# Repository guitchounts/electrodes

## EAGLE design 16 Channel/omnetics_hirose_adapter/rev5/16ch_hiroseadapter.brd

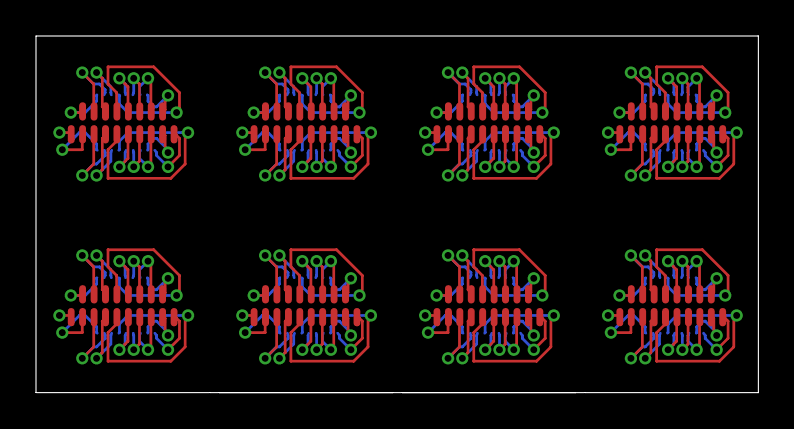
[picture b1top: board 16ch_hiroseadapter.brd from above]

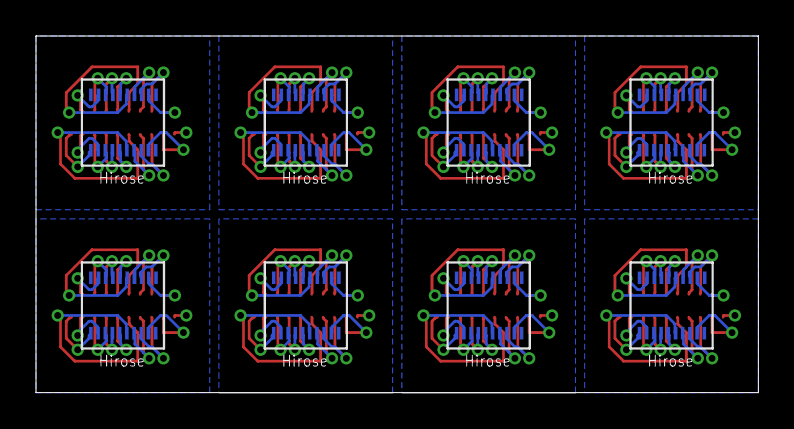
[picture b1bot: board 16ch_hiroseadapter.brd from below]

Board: 2 copper layers, 40.1 x 19.8 mm, 16 parts (8 on the bottom side), 144 nets.

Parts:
U$1, U$3, U$5, U$7, U$9, U$11, U$13, U$15: HIROSE_DF40_70PIN; HIROSE_DF40C-70DS
U$2, U$4, U$6, U$8, U$10, U$12, U$14, U$16: OMNETICS_FE18

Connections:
unnamed: U$1.P$10, U$2.P$18
unnamed: U$1.P$9, U$2.P$8
unnamed: U$1.P$8, U$2.P$7
unnamed: U$1.P$7, U$2.P$6
unnamed: U$1.P$6, U$2.P$5
unnamed: U$1.P$5, U$2.P$4
unnamed: U$1.P$4, U$2.P$3
unnamed: U$1.P$3, U$2.P$2
unnamed: U$1.P$2, U$2.P$1
unnamed: U$1.P$1, U$2.P$17
unnamed: U$1.P$44, U$2.P$9
unnamed: U$1.P$43, U$2.P$10
unnamed: U$1.P$42, U$2.P$11
unnamed: U$1.P$41, U$2.P$12
unnamed: U$1.P$40, U$2.P$13
unnamed: U$1.P$39, U$2.P$14
unnamed: U$1.P$38, U$2.P$15
unnamed: U$1.P$37, U$2.P$16
unnamed: U$3.P$10, U$4.P$18
unnamed: U$3.P$9, U$4.P$8
unnamed: U$3.P$8, U$4.P$7
unnamed: U$3.P$7, U$4.P$6
unnamed: U$3.P$6, U$4.P$5
unnamed: U$3.P$5, U$4.P$4
unnamed: U$3.P$4, U$4.P$3
unnamed: U$3.P$3, U$4.P$2
unnamed: U$3.P$2, U$4.P$1
unnamed: U$3.P$1, U$4.P$17
unnamed: U$3.P$44, U$4.P$9
unnamed: U$3.P$43, U$4.P$10
unnamed: U$3.P$42, U$4.P$11
unnamed: U$3.P$41, U$4.P$12
unnamed: U$3.P$40, U$4.P$13
unnamed: U$3.P$39, U$4.P$14
unnamed: U$3.P$38, U$4.P$15
unnamed: U$3.P$37, U$4.P$16
unnamed: U$5.P$10, U$6.P$18
unnamed: U$5.P$9, U$6.P$8
unnamed: U$5.P$8, U$6.P$7
unnamed: U$5.P$7, U$6.P$6
unnamed: U$5.P$6, U$6.P$5
unnamed: U$5.P$5, U$6.P$4
unnamed: U$5.P$4, U$6.P$3
unnamed: U$5.P$3, U$6.P$2
unnamed: U$5.P$2, U$6.P$1
unnamed: U$5.P$1, U$6.P$17
unnamed: U$5.P$44, U$6.P$9
unnamed: U$5.P$43, U$6.P$10
unnamed: U$5.P$42, U$6.P$11
unnamed: U$5.P$41, U$6.P$12
unnamed: U$5.P$40, U$6.P$13
unnamed: U$5.P$39, U$6.P$14
unnamed: U$5.P$38, U$6.P$15
unnamed: U$5.P$37, U$6.P$16
unnamed: U$7.P$10, U$8.P$18
unnamed: U$7.P$9, U$8.P$8
unnamed: U$7.P$8, U$8.P$7
unnamed: U$7.P$7, U$8.P$6
unnamed: U$7.P$6, U$8.P$5
unnamed: U$7.P$5, U$8.P$4
unnamed: U$7.P$4, U$8.P$3
unnamed: U$7.P$3, U$8.P$2
unnamed: U$7.P$2, U$8.P$1
unnamed: U$7.P$1, U$8.P$17
unnamed: U$7.P$44, U$8.P$9
unnamed: U$7.P$43, U$8.P$10
unnamed: U$7.P$42, U$8.P$11
unnamed: U$7.P$41, U$8.P$12
unnamed: U$7.P$40, U$8.P$13
unnamed: U$7.P$39, U$8.P$14
unnamed: U$7.P$38, U$8.P$15
unnamed: U$7.P$37, U$8.P$16
unnamed: U$9.P$10, U$10.P$18
unnamed: U$9.P$9, U$10.P$8
unnamed: U$9.P$8, U$10.P$7
unnamed: U$9.P$7, U$10.P$6
unnamed: U$9.P$6, U$10.P$5
unnamed: U$9.P$5, U$10.P$4
unnamed: U$9.P$4, U$10.P$3
unnamed: U$9.P$3, U$10.P$2
unnamed: U$9.P$2, U$10.P$1
unnamed: U$9.P$1, U$10.P$17
unnamed: U$9.P$44, U$10.P$9
unnamed: U$9.P$43, U$10.P$10
unnamed: U$9.P$42, U$10.P$11
unnamed: U$9.P$41, U$10.P$12
unnamed: U$9.P$40, U$10.P$13
unnamed: U$9.P$39, U$10.P$14
unnamed: U$9.P$38, U$10.P$15
unnamed: U$9.P$37, U$10.P$16
unnamed: U$11.P$10, U$12.P$18
unnamed: U$11.P$9, U$12.P$8
unnamed: U$11.P$8, U$12.P$7
unnamed: U$11.P$7, U$12.P$6
unnamed: U$11.P$6, U$12.P$5
unnamed: U$11.P$5, U$12.P$4
unnamed: U$11.P$4, U$12.P$3
unnamed: U$11.P$3, U$12.P$2
unnamed: U$11.P$2, U$12.P$1
unnamed: U$11.P$1, U$12.P$17
unnamed: U$11.P$44, U$12.P$9
unnamed: U$11.P$43, U$12.P$10
unnamed: U$11.P$42, U$12.P$11
unnamed: U$11.P$41, U$12.P$12
unnamed: U$11.P$40, U$12.P$13
unnamed: U$11.P$39, U$12.P$14
unnamed: U$11.P$38, U$12.P$15
unnamed: U$11.P$37, U$12.P$16
unnamed: U$13.P$10, U$14.P$18
unnamed: U$13.P$9, U$14.P$8
unnamed: U$13.P$8, U$14.P$7
unnamed: U$13.P$7, U$14.P$6
unnamed: U$13.P$6, U$14.P$5
unnamed: U$13.P$5, U$14.P$4
unnamed: U$13.P$4, U$14.P$3
unnamed: U$13.P$3, U$14.P$2
unnamed: U$13.P$2, U$14.P$1
unnamed: U$13.P$1, U$14.P$17
unnamed: U$13.P$44, U$14.P$9
unnamed: U$13.P$43, U$14.P$10
unnamed: U$13.P$42, U$14.P$11
unnamed: U$13.P$41, U$14.P$12
unnamed: U$13.P$40, U$14.P$13
unnamed: U$13.P$39, U$14.P$14
unnamed: U$13.P$38, U$14.P$15
unnamed: U$13.P$37, U$14.P$16
unnamed: U$15.P$10, U$16.P$18
unnamed: U$15.P$9, U$16.P$8
unnamed: U$15.P$8, U$16.P$7
unnamed: U$15.P$7, U$16.P$6
unnamed: U$15.P$6, U$16.P$5
unnamed: U$15.P$5, U$16.P$4
unnamed: U$15.P$4, U$16.P$3
unnamed: U$15.P$3, U$16.P$2
unnamed: U$15.P$2, U$16.P$1
unnamed: U$15.P$1, U$16.P$17
unnamed: U$15.P$44, U$16.P$9
unnamed: U$15.P$43, U$16.P$10
unnamed: U$15.P$42, U$16.P$11
unnamed: U$15.P$41, U$16.P$12
unnamed: U$15.P$40, U$16.P$13
unnamed: U$15.P$39, U$16.P$14
unnamed: U$15.P$38, U$16.P$15
unnamed: U$15.P$37, U$16.P$16

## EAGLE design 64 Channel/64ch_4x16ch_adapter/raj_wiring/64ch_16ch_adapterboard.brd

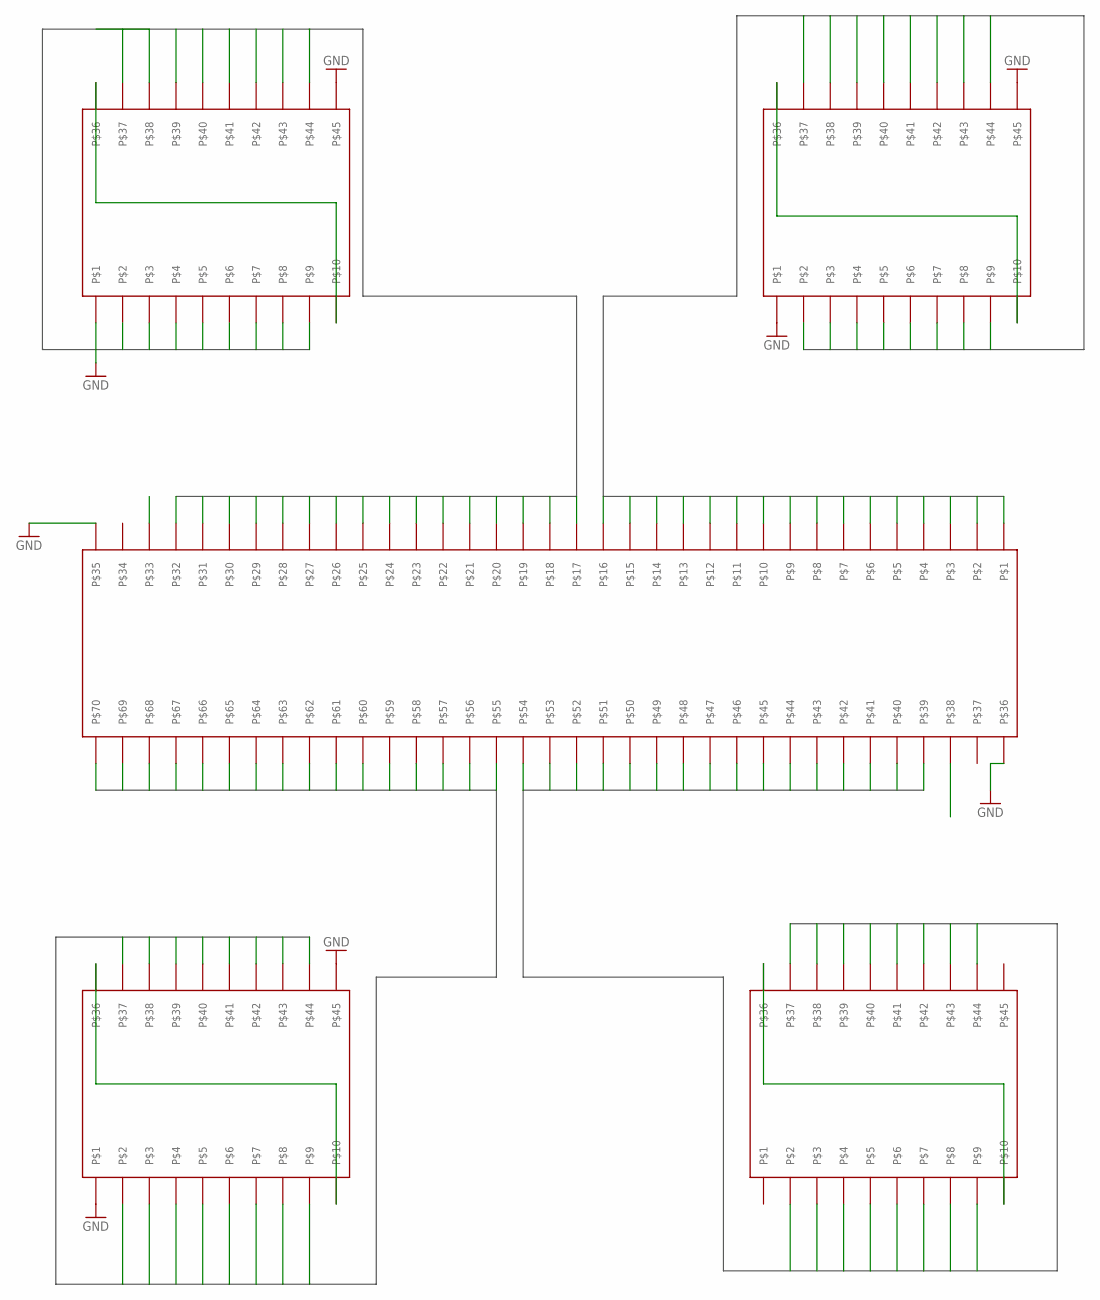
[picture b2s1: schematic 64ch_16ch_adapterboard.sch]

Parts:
U$1: HIROSE_DF40_70PIN; HIROSE_DF40C-70DS
U$2, U$3, U$4, U$5: HIROSE_DF40_20PIN; HIROSE_DF40C-70DS

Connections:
A0: U$1.P$18, U$3.P$44
A1: U$1.P$17, U$3.P$9
A2: U$1.P$32, U$3.P$8
A3: U$1.P$31, U$3.P$7
A4: U$1.P$30, U$3.P$6
A5: U$1.P$29, U$3.P$5
A6: U$1.P$28, U$3.P$4
A7: U$1.P$27, U$3.P$3
A8: U$1.P$26, U$3.P$2
A9: U$1.P$25, U$3.P$37
A10: U$1.P$22, U$3.P$38
A11: U$1.P$21, U$3.P$39
A12: U$1.P$23, U$3.P$40
A13: U$1.P$20, U$3.P$41
A14: U$1.P$24, U$3.P$42
A15: U$1.P$19, U$3.P$43
B0: U$1.P$3, U$2.P$37
B1: U$1.P$4, U$2.P$2
B2: U$1.P$5, U$2.P$3
B3: U$1.P$6, U$2.P$4
B4: U$1.P$7, U$2.P$5
B5: U$1.P$8, U$2.P$6
B6: U$1.P$9, U$2.P$7
B7: U$1.P$10, U$2.P$8
B8: U$1.P$11, U$2.P$9
B9: U$1.P$12, U$2.P$44
B10: U$1.P$15, U$2.P$43
B11: U$1.P$16, U$2.P$42
B12: U$1.P$14, U$2.P$41
B13: U$1.P$1, U$2.P$40
B14: U$1.P$13, U$2.P$39
B15: U$1.P$2, U$2.P$38
C0: U$1.P$69, U$5.P$9
C1: U$1.P$68, U$5.P$44
C2: U$1.P$67, U$5.P$43
C3: U$1.P$66, U$5.P$42
C4: U$1.P$65, U$5.P$41
C5: U$1.P$64, U$5.P$40
C6: U$1.P$63, U$5.P$39
C7: U$1.P$62, U$5.P$38
C8: U$1.P$61, U$5.P$37
C9: U$1.P$60, U$5.P$2
C10: U$1.P$57, U$5.P$3
C11: U$1.P$56, U$5.P$4
C12: U$1.P$58, U$5.P$5
C13: U$1.P$55, U$5.P$6
C14: U$1.P$59, U$5.P$7
C15: U$1.P$70, U$5.P$8
D0: U$1.P$54, U$4.P$2
D1: U$1.P$39, U$4.P$37
D2: U$1.P$40, U$4.P$38
D3: U$1.P$41, U$4.P$39
D4: U$1.P$42, U$4.P$40
D5: U$1.P$43, U$4.P$41
D6: U$1.P$44, U$4.P$42
D7: U$1.P$45, U$4.P$43
D8: U$1.P$46, U$4.P$44
D9: U$1.P$47, U$4.P$9
D10: U$1.P$50, U$4.P$8
D11: U$1.P$51, U$4.P$7
D12: U$1.P$49, U$4.P$6
D13: U$1.P$52, U$4.P$5
D14: U$1.P$48, U$4.P$4
D15: U$1.P$53, U$4.P$3
GND: U$1.P$35, U$1.P$36, U$2.P$1, U$2.P$45, U$3.P$1, U$3.P$45, U$5.P$1, U$5.P$45
REF: U$1.P$33, U$1.P$38, U$2.P$10, U$2.P$36, U$3.P$10, U$3.P$36, U$4.P$10, U$4.P$36, U$5.P$10, U$5.P$36

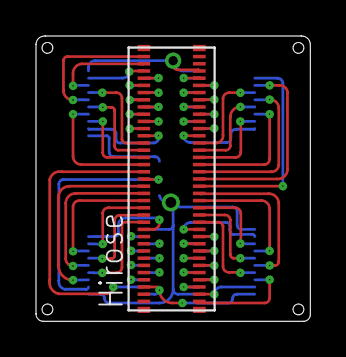
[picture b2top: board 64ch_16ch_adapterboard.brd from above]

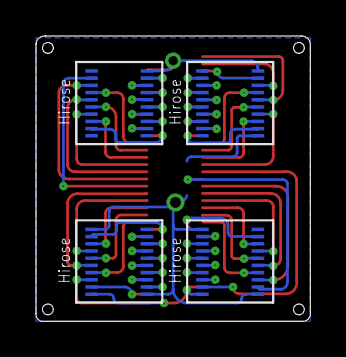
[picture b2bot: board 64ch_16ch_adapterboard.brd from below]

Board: 2 copper layers, 15.2 x 15.8 mm, 5 parts (4 on the bottom side), 66 nets.

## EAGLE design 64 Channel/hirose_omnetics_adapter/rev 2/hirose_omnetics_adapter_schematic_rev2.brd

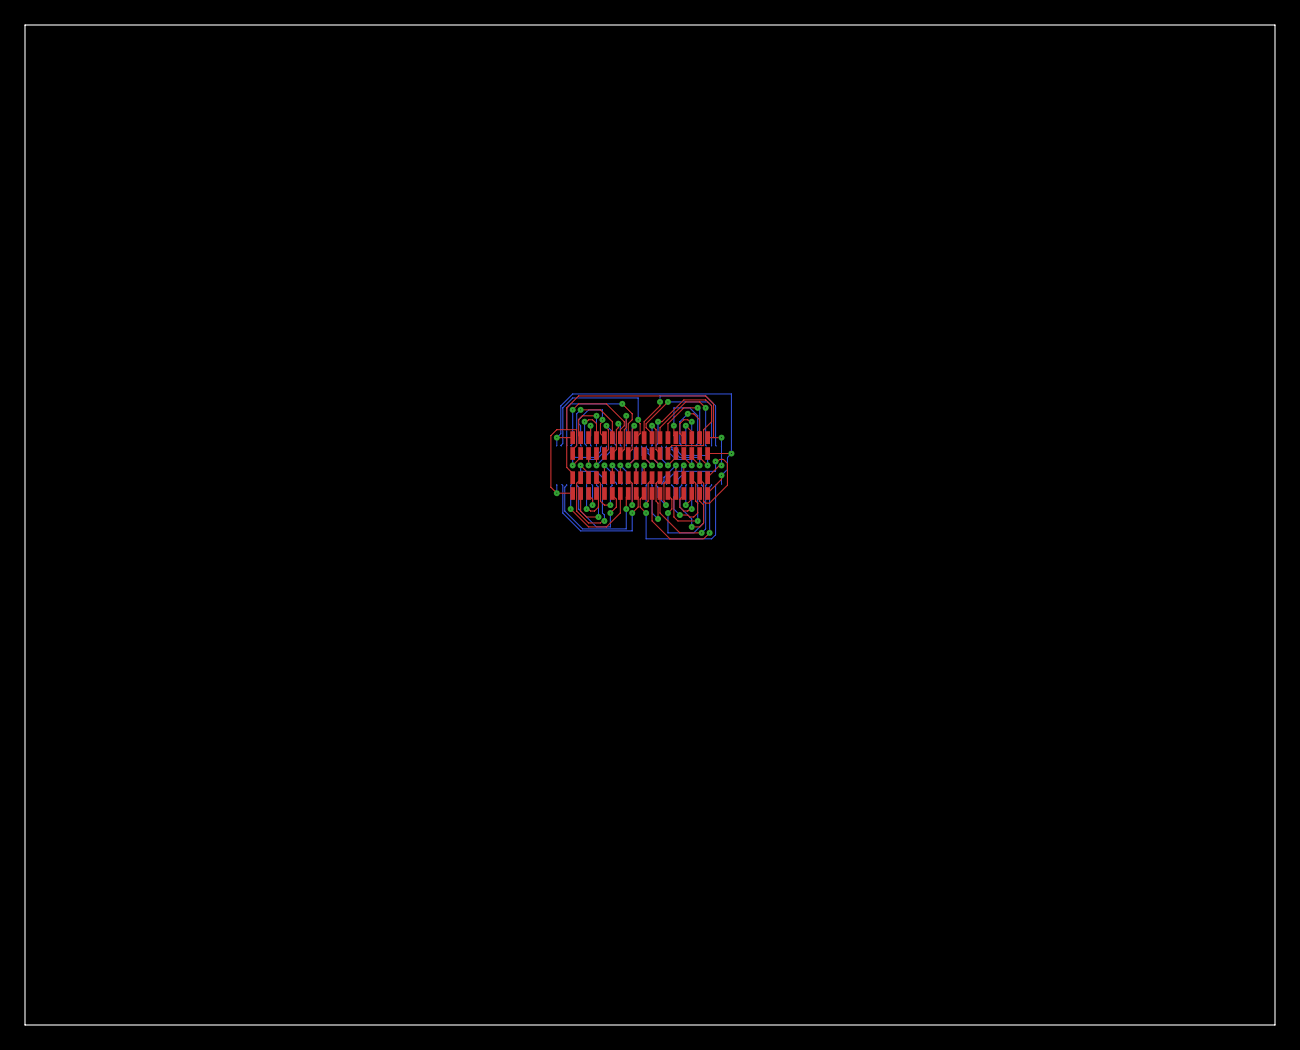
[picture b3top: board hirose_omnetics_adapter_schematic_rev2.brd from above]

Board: 2 copper layers, 100.0 x 80.0 mm, 3 parts (1 on the bottom side), 66 nets.

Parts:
U$1: HIROSE_DF40_70PIN; HIROSE_DF40C-70DS
U$2, U$3: OMNETICS_A79026; OMNETICS_A79026-001

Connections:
A0: U$1.P$69, U$2.P$10
A1: U$1.P$68, U$2.P$11
A2: U$1.P$67, U$2.P$12
A3: U$1.P$66, U$2.P$13
A4: U$1.P$65, U$2.P$14
A5: U$1.P$64, U$2.P$15
A6: U$1.P$63, U$2.P$16
A7: U$1.P$62, U$2.P$17
B0: U$1.P$38, U$2.P$9
B1: U$1.P$39, U$2.P$8
B2: U$1.P$40, U$2.P$7
B3: U$1.P$41, U$2.P$6
B4: U$1.P$42, U$2.P$5
B5: U$1.P$43, U$2.P$4
B6: U$1.P$44, U$2.P$3
B7: U$1.P$45, U$2.P$2
C0: U$1.P$34, U$3.P$28
C1: U$1.P$33, U$3.P$29
C2: U$1.P$32, U$3.P$30
C3: U$1.P$31, U$3.P$31
C4: U$1.P$30, U$3.P$32
C5: U$1.P$29, U$3.P$33
C6: U$1.P$28, U$3.P$34
C7: U$1.P$27, U$3.P$35
D0: U$1.P$3, U$3.P$27
D1: U$1.P$4, U$3.P$26
D2: U$1.P$5, U$3.P$25
D3: U$1.P$6, U$3.P$24
D4: U$1.P$7, U$3.P$23
D5: U$1.P$8, U$3.P$22
D6: U$1.P$9, U$3.P$21
D7: U$1.P$10, U$3.P$20
GND: U$1.P$35, U$1.P$37, U$2.P$1, U$2.P$36, U$3.P$1, U$3.P$36
unnamed: U$1.P$61, U$2.P$35
unnamed: U$1.P$2, U$1.P$70, U$2.P$18, U$2.P$19, U$3.P$18, U$3.P$19
unnamed: U$1.P$60, U$2.P$34
unnamed: U$1.P$59, U$2.P$33
unnamed: U$1.P$58, U$2.P$32
unnamed: U$1.P$57, U$2.P$31
unnamed: U$1.P$56, U$2.P$30
unnamed: U$1.P$55, U$2.P$29
unnamed: U$1.P$54, U$2.P$28
unnamed: U$1.P$53, U$2.P$27
unnamed: U$1.P$52, U$2.P$26
unnamed: U$1.P$51, U$2.P$25
unnamed: U$1.P$50, U$2.P$24
unnamed: U$1.P$49, U$2.P$23
unnamed: U$1.P$48, U$2.P$22
unnamed: U$1.P$47, U$2.P$21
unnamed: U$1.P$46, U$2.P$20
unnamed: U$1.P$26, U$3.P$17
unnamed: U$1.P$25, U$3.P$16
unnamed: U$1.P$24, U$3.P$15
unnamed: U$1.P$23, U$3.P$14
unnamed: U$1.P$22, U$3.P$13
unnamed: U$1.P$21, U$3.P$12
unnamed: U$1.P$20, U$3.P$11
unnamed: U$1.P$19, U$3.P$10
unnamed: U$1.P$18, U$3.P$9
unnamed: U$1.P$17, U$3.P$8
unnamed: U$1.P$16, U$3.P$7
unnamed: U$1.P$15, U$3.P$6
unnamed: U$1.P$14, U$3.P$5
unnamed: U$1.P$13, U$3.P$4
unnamed: U$1.P$12, U$3.P$3
unnamed: U$1.P$11, U$3.P$2

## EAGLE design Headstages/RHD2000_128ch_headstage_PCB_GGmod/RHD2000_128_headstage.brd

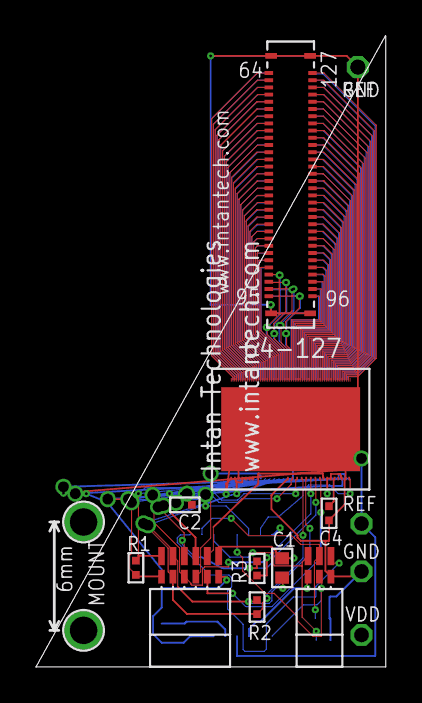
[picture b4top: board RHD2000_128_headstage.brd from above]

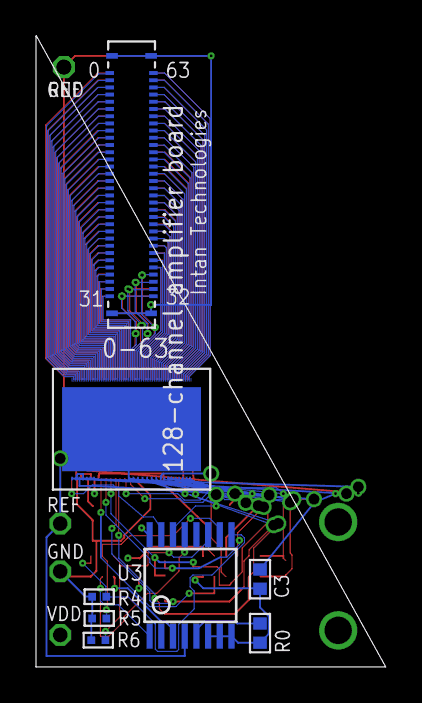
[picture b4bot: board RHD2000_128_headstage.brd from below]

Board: 4 copper layers, 19.4 x 35.1 mm, 25 parts (9 on the bottom side), 151 nets.

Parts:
C1, C3: 100n; 0402
C2, C4: 10n; 0201
GND, GND.: TESTPOINT_SMALL
H1, H2: MOUNTING_HOLE_60MIL
R0: 0; 0402
R1, R2, R3: 100; 0201
R4, R5, R6: 100k; 0201
REF, REF.: TESTPOINT_SMALL
S1, S2: MOLEX_SLIMSTACK_64
S3: RHD2000-CABLE-AMP-SIDE; OMNETICS_PZN-12-AA
S4: OMNETICS_PZN-06_SMD; OMNETICS_PZN-06-AA
U1, U2: RHD2164_COB
U3: 74HC4053_TSSOP-16; TSSOP-16
VDD: TESTPOINT_SMALL

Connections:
CS+: R1.2, S3.T1, U1.B10, U2.B10
CS-: R1.1, S3.B1, U1.B9, U2.B9
ELEC_TEST1: U1.B23, U3.14
ELEC_TEST2: U2.B23, U3.15
GND: C1.2, C2.2, C3.2, C4.2, GND.1, GND..1, R0.1, R4.1, R5.1, R6.1, S1.MECH1, S1.MECH2, S1.MECH3, S1.MECH4, S2.MECH1, S2.MECH2, S2.MECH3, S2.MECH4, S3.B6, S4.B3, U1.B3, U1.B8, U1.B22, U1.CENTER, U2.B3, U2.B8, U2.B22, U2.CENTER, U3.6, U3.7, U3.8
MISO1+: S3.T4, U1.B16
MISO1-: S3.B4, U1.B15
MISO2+: S3.T5, U2.B16
MISO2-: S3.B5, U2.B15
MOSI+: R3.2, S3.T3, U1.B14, U2.B14
MOSI-: R3.1, S3.B3, U1.B13, U2.B13
unnamed: C4.1, U2.B19
unnamed: S1.1, U1.0
unnamed: S1.2, U1.1
unnamed: S1.3, U1.2
unnamed: S1.4, U1.3
unnamed: S1.5, U1.4
unnamed: S1.6, U1.5
unnamed: S1.7, U1.6
unnamed: S1.8, U1.7
unnamed: S1.9, U1.8
unnamed: S2.1, U2.0
unnamed: S1.10, U1.9
unnamed: S1.11, U1.10
unnamed: S1.12, U1.11
unnamed: S1.13, U1.12
unnamed: S1.14, U1.13
unnamed: S1.15, U1.14
unnamed: S1.16, U1.15
unnamed: S1.17, U1.16
unnamed: S1.18, U1.17
unnamed: S1.19, U1.18
unnamed: S1.20, U1.19
unnamed: S1.21, U1.20
unnamed: S1.22, U1.21
unnamed: S1.23, U1.22
unnamed: S1.24, U1.23
unnamed: S1.25, U1.24
unnamed: S1.26, U1.25
unnamed: S1.27, U1.26
unnamed: S1.28, U1.27
unnamed: S1.38, U1.37
unnamed: S1.39, U1.38
unnamed: S1.64, U1.63
unnamed: S1.63, U1.62
unnamed: S2.2, U2.1
unnamed: S2.3, U2.2
unnamed: S2.4, U2.3
unnamed: S2.5, U2.4
unnamed: S2.6, U2.5
unnamed: S2.7, U2.6
unnamed: S1.62, U1.61
unnamed: C2.1, U1.B19
unnamed: S1.61, U1.60
unnamed: S1.60, U1.59
unnamed: S1.59, U1.58
unnamed: S1.58, U1.57
unnamed: S1.57, U1.56
unnamed: S1.56, U1.55
unnamed: S1.55, U1.54
unnamed: S1.54, U1.53
unnamed: S1.53, U1.52
unnamed: S1.52, U1.51
unnamed: S1.51, U1.50
unnamed: S1.50, U1.49
unnamed: S1.49, U1.48
unnamed: S1.48, U1.47
unnamed: S1.47, U1.46
unnamed: S1.46, U1.45
unnamed: S1.45, U1.44
unnamed: S1.44, U1.43
unnamed: S1.43, U1.42
unnamed: S1.42, U1.41
unnamed: S1.41, U1.40
unnamed: S1.40, U1.39
unnamed: S1.32, U1.31
unnamed: S1.31, U1.30
unnamed: S1.30, U1.29
unnamed: S1.29, U1.28
unnamed: S1.33, U1.32
unnamed: S1.34, U1.33
unnamed: S1.35, U1.34
unnamed: S1.36, U1.35
unnamed: S1.37, U1.36
unnamed: S2.8, U2.7
unnamed: S2.9, U2.8
unnamed: S2.10, U2.9
unnamed: S2.11, U2.10
unnamed: S2.12, U2.11
unnamed: S2.13, U2.12
unnamed: S2.14, U2.13
unnamed: S2.15, U2.14
unnamed: S2.16, U2.15
unnamed: S2.17, U2.16
unnamed: S2.18, U2.17
unnamed: S2.19, U2.18
unnamed: S2.20, U2.19
unnamed: S2.21, U2.20
unnamed: S2.22, U2.21
unnamed: S2.23, U2.22
unnamed: S2.24, U2.23
unnamed: S2.25, U2.24
unnamed: S2.26, U2.25
unnamed: S2.27, U2.26
unnamed: S2.28, U2.27
unnamed: S2.38, U2.37
unnamed: S2.39, U2.38
unnamed: S2.64, U2.63
unnamed: S2.63, U2.62
unnamed: S2.62, U2.61
unnamed: S2.61, U2.60
unnamed: S2.60, U2.59
unnamed: S2.59, U2.58
unnamed: S2.58, U2.57
unnamed: S2.57, U2.56
unnamed: S2.56, U2.55
unnamed: S2.55, U2.54
unnamed: S2.54, U2.53
unnamed: S2.53, U2.52
unnamed: S2.52, U2.51
unnamed: S2.51, U2.50
unnamed: S2.50, U2.49
unnamed: S2.49, U2.48
unnamed: S2.48, U2.47
unnamed: S2.47, U2.46
unnamed: S2.46, U2.45
unnamed: S2.45, U2.44
unnamed: S2.44, U2.43
unnamed: S2.43, U2.42
unnamed: S2.42, U2.41
unnamed: S2.41, U2.40
unnamed: S2.40, U2.39
unnamed: S2.32, U2.31
unnamed: S2.31, U2.30
unnamed: S2.30, U2.29
unnamed: S2.29, U2.28
unnamed: S2.33, U2.32
unnamed: S2.34, U2.33
unnamed: S2.35, U2.34
unnamed: S2.36, U2.35
unnamed: S2.37, U2.36
unnamed: R6.2, S4.T1, U3.11
unnamed: R5.2, S4.T2, U3.10
unnamed: R4.2, S4.T3, U3.9
unnamed: R0.2, U3.5
unnamed: S4.B1, U3.3
unnamed: S4.B2, U3.1, U3.13
REF: REF.1, REF..1, U1.B1, U2.B1, U3.4
SCLK+: R2.2, S3.T2, U1.B12, U2.B12
SCLK-: R2.1, S3.B2, U1.B11, U2.B11
VCC: C1.1, C3.1, S3.T6, U1.B2, U1.B4, U1.B5, U1.B6, U1.B7, U1.B17, U1.B18, U1.B21, U2.B2, U2.B4, U2.B5, U2.B6, U2.B7, U2.B17, U2.B18, U2.B21, U3.16, VDD.1
